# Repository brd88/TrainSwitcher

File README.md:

# TrainSwitcher
Microcomputer based management of train switches

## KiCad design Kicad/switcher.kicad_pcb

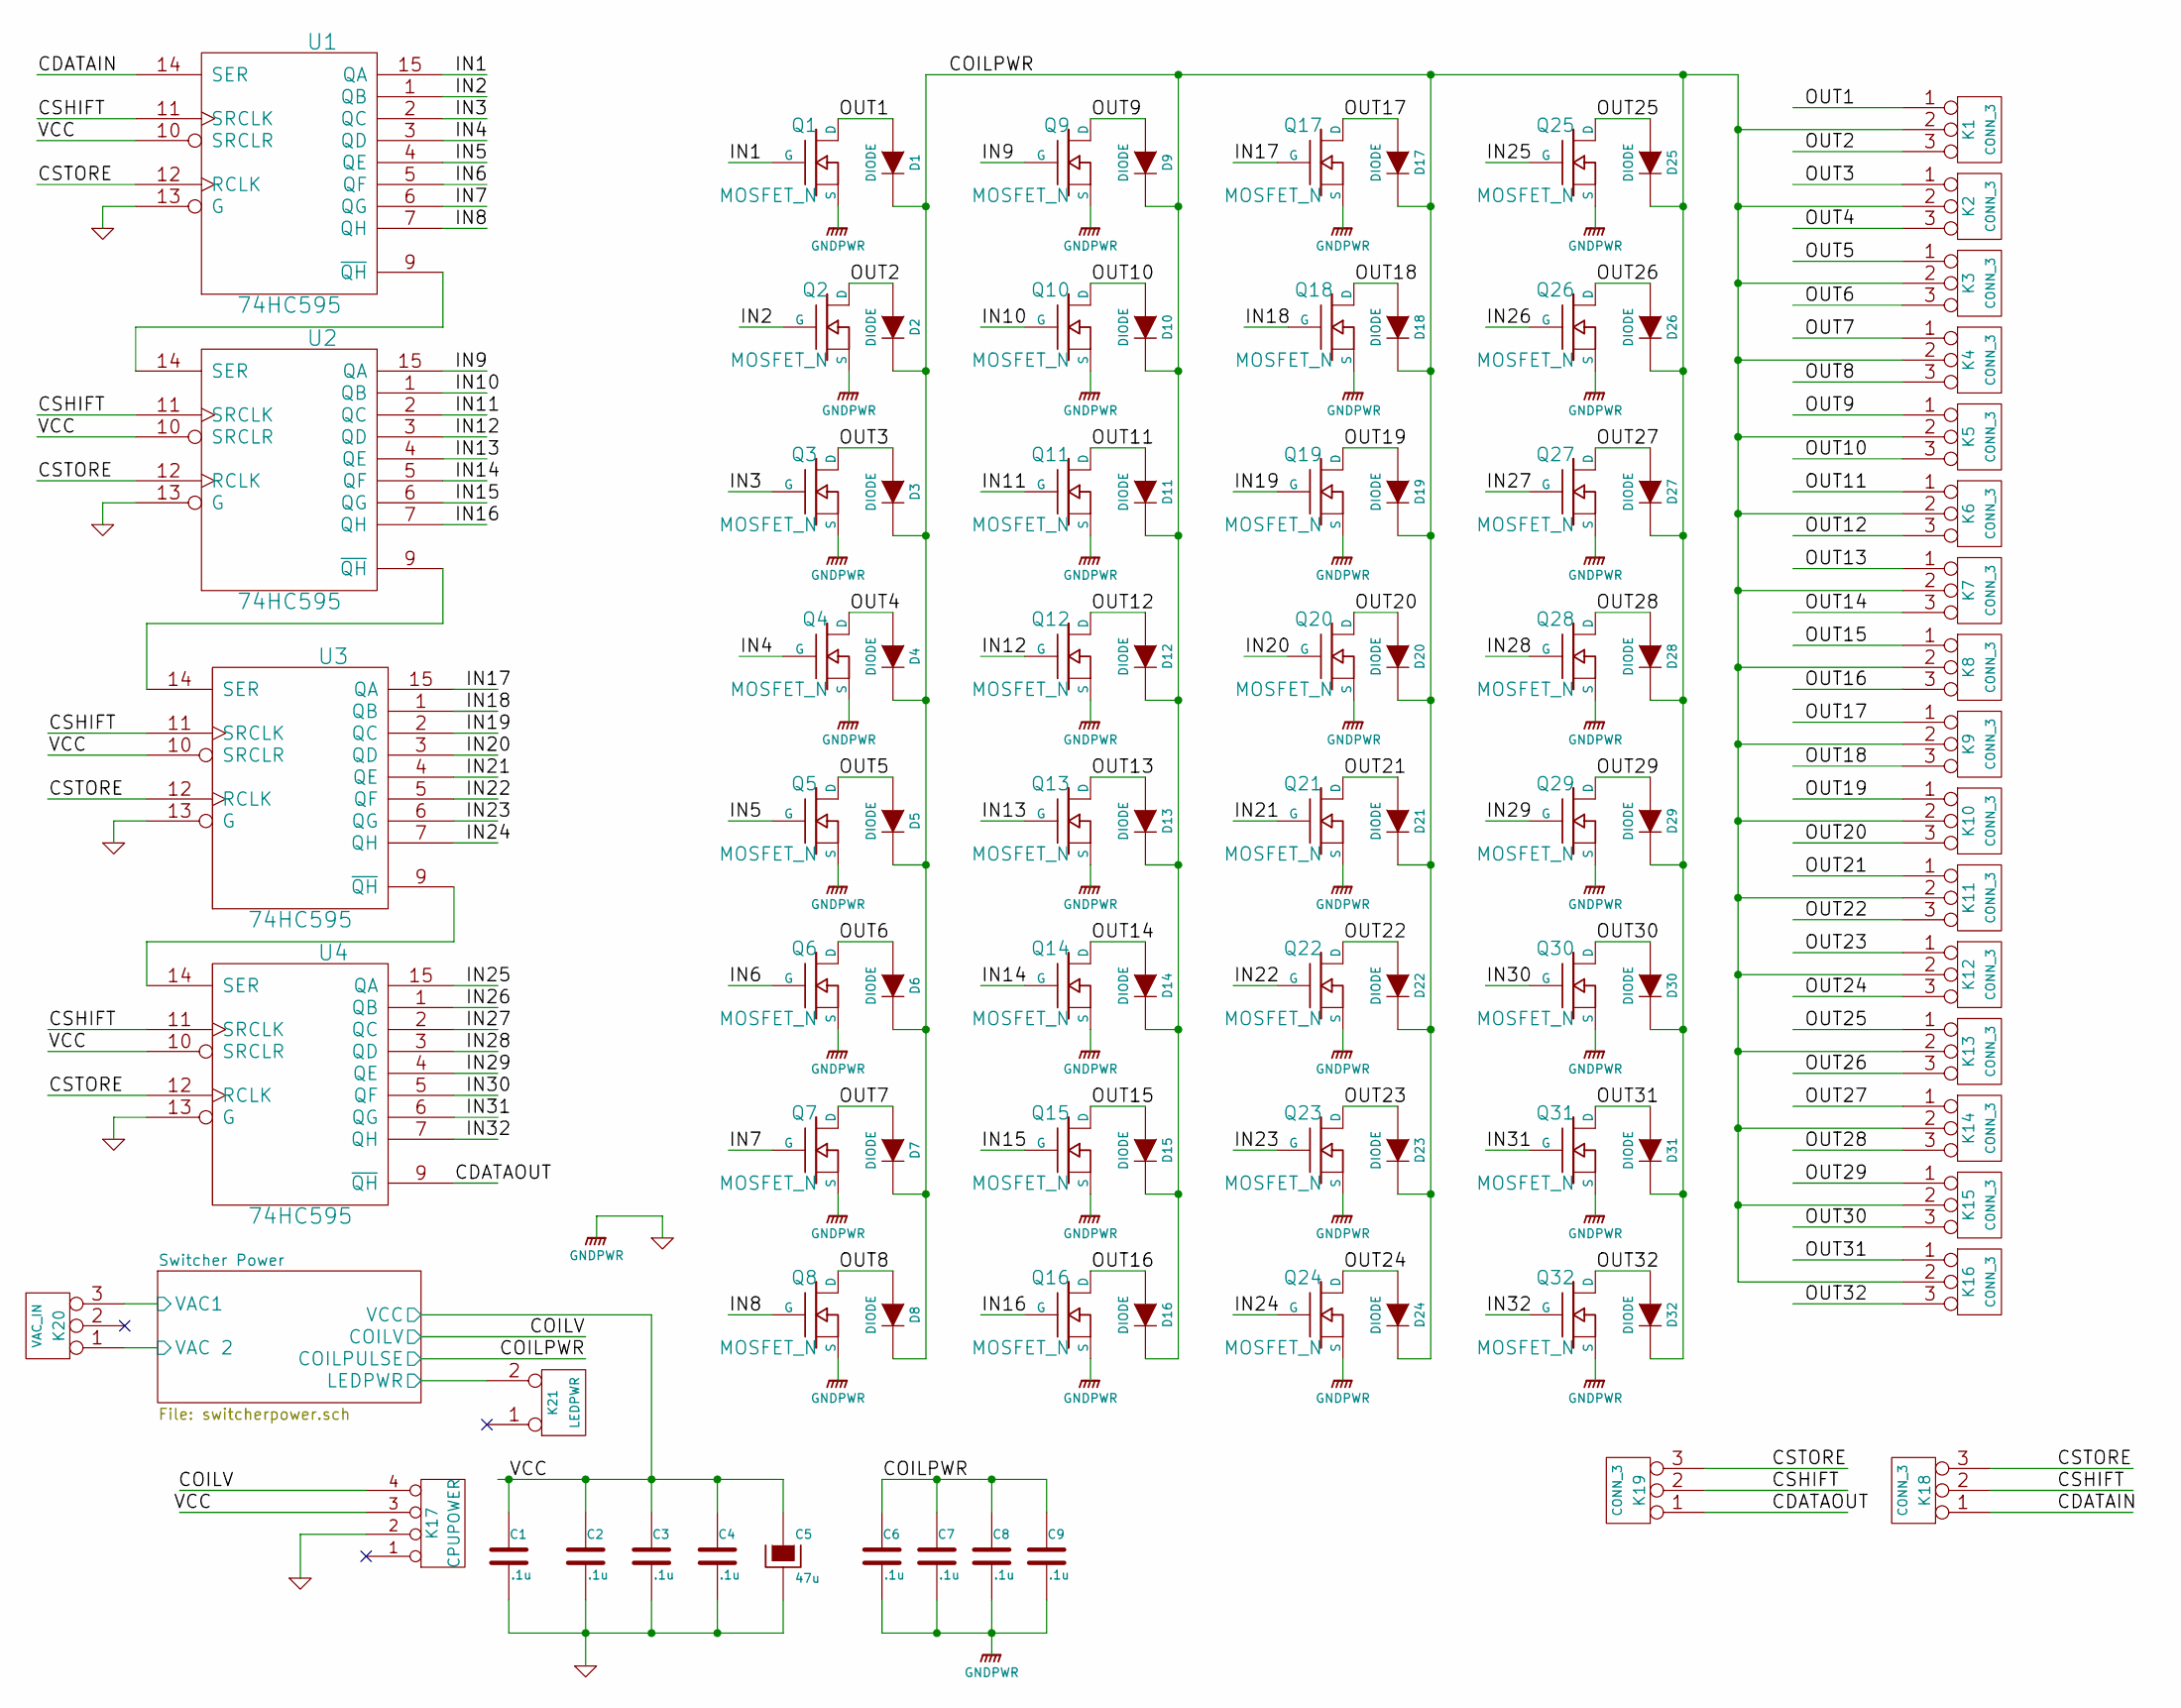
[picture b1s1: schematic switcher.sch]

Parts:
C1, C2, C3, C4, C6, C7, C8, C9: .1u
C5: 47u
D1, D2, D3, D4, D5, D6, D7, D8, D9, D10, D11, D12, D13, D14, D15, D16, D17, D18, D19, D20, D21, D22, D23, D24, D25, D26, D27, D28, D29, D30, D31, D32: DIODE
K1, K2, K3, K4, K5, K6, K7, K8, K9, K10, K11, K12, K13, K14, K15, K16, K18, K19: CONN_3
K17: CPUPOWER
K20: VAC_IN
K21: LEDPWR
Q1, Q2, Q3, Q4, Q5, Q6, Q7, Q8, Q9, Q10, Q11, Q12, Q13, Q14, Q15, Q16, Q17, Q18, Q19, Q20, Q21, Q22, Q23, Q24, Q25, Q26, Q27, Q28, Q29, Q30, Q31, Q32: MOSFET_N
U1, U2, U3, U4: 74HC595

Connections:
/CDATAIN: K18.1, U1.14 (SER)
/CDATAOUT: K19.1, U4.9 (~QH)
/CSHIFT: K18.2 (PM), K19.2 (PM), U1.11 (SRCLK), U2.11 (SRCLK), U3.11 (SRCLK), U4.11 (SRCLK)
/CSTORE: K18.3, K19.3, U1.12 (RCLK), U2.12 (RCLK), U3.12 (RCLK), U4.12 (RCLK)
/IN1: Q1.G, U1.15 (QA)
/IN2: Q2.G, U1.1 (QB)
/IN3: Q3.G, U1.2 (QC)
/IN4: Q4.G, U1.3 (QD)
/IN5: Q5.G, U1.4 (QE)
/IN6: Q6.G, U1.5 (QF)
/IN7: Q7.G, U1.6 (QG)
/IN8: Q8.G, U1.7 (QH)
/IN9: Q9.G, U2.15 (QA)
/IN10: Q10.G, U2.1 (QB)
/IN11: Q11.G, U2.2 (QC)
/IN12: Q12.G, U2.3 (QD)
/IN13: Q13.G, U2.4 (QE)
/IN14: Q14.G, U2.5 (QF)
/IN15: Q15.G, U2.6 (QG)
/IN16: Q16.G, U2.7 (QH)
/IN17: Q17.G, U3.15 (QA)
/IN18: Q18.G, U3.1 (QB)
/IN19: Q19.G, U3.2 (QC)
/IN20: Q20.G, U3.3 (QD)
/IN21: Q21.G, U3.4 (QE)
/IN22: Q22.G, U3.5 (QF)
/IN23: Q23.G, U3.6 (QG)
/IN24: Q24.G, U3.7 (QH)
/IN25: Q25.G, U4.15 (QA)
/IN26: Q26.G, U4.1 (QB)
/IN27: Q27.G, U4.2 (QC)
/IN28: Q28.G, U4.3 (QD)
/IN29: Q29.G, U4.4 (QE)
/IN30: Q30.G, U4.5 (QF)
/IN31: Q31.G, U4.6 (QG)
/IN32: Q32.G, U4.7 (QH)
/OUT1: D1.1 (A), K1.1, Q1.D
/OUT2: D2.1 (A), K1.3, Q2.D
/OUT3: D3.1 (A), K2.1, Q3.D
/OUT4: D4.1 (A), K2.3, Q4.D
/OUT5: D5.1 (A), K3.1, Q5.D
/OUT6: D6.1 (A), K3.3, Q6.D
/OUT7: D7.1 (A), K4.1, Q7.D
/OUT8: D8.1 (A), K4.3, Q8.D
/OUT9: D9.1 (A), K5.1, Q9.D
/OUT10: D10.1 (A), K5.3, Q10.D
/OUT11: D11.1 (A), K6.1, Q11.D
/OUT12: D12.1 (A), K6.3, Q12.D
/OUT13: D13.1 (A), K7.1, Q13.D
/OUT14: D14.1 (A), K7.3, Q14.D
/OUT15: D15.1 (A), K8.1, Q15.D
/OUT16: D16.1 (A), K8.3, Q16.D
/OUT17: D17.1 (A), K9.1, Q17.D
/OUT18: D18.1 (A), K9.3, Q18.D
/OUT19: D19.1 (A), K10.1, Q19.D
/OUT20: D20.1 (A), K10.3, Q20.D
/OUT21: D21.1 (A), K11.1, Q21.D
/OUT22: D22.1 (A), K11.3, Q22.D
/OUT23: D23.1 (A), K12.1, Q23.D
/OUT24: D24.1 (A), K12.3, Q24.D
/OUT25: D25.1 (A), K13.1, Q25.D
/OUT26: D26.1 (A), K13.3, Q26.D
/OUT27: D27.1 (A), K14.1, Q27.D
/OUT28: D28.1 (A), K14.3, Q28.D
/OUT29: D29.1 (A), K15.1, Q29.D
/OUT30: D30.1 (A), K15.3, Q30.D
/OUT31: D31.1 (A), K16.1, Q31.D
/OUT32: D32.1 (A), K16.3, Q32.D
/Switcher Power/COILPULSE: C6.1, C7.1, C8.1, C9.1, D1.2 (K), D2.2 (K), D3.2 (K), D4.2 (K), D5.2 (K), D6.2 (K), D7.2 (K), D8.2 (K), D9.2 (K), D10.2 (K), D11.2 (K), D12.2 (K), D13.2 (K), D14.2 (K), D15.2 (K), D16.2 (K), D17.2 (K), D18.2 (K), D19.2 (K), D20.2 (K), D21.2 (K), D22.2 (K), D23.2 (K), D24.2 (K), D25.2 (K), D26.2 (K), D27.2 (K), D28.2 (K), D29.2 (K), D30.2 (K), D31.2 (K), D32.2 (K), K1.2 (PM), K2.2 (PM), K3.2 (PM), K4.2 (PM), K5.2 (PM), K6.2 (PM), K7.2 (PM), K8.2 (PM), K9.2 (PM), K10.2 (PM), K11.2 (PM), K12.2 (PM), K13.2 (PM), K14.2 (PM), K15.2 (PM), K16.2 (PM); also elsewhere on the board
/Switcher Power/COILV: K17.4; also elsewhere on the board
/Switcher Power/LEDPWR: K21.2 (PM); also elsewhere on the board
/Switcher Power/VAC1: K20.3; also elsewhere on the board
/Switcher Power/VAC 2: K20.1; also elsewhere on the board
GND: C1.2, C2.2, C3.2, C4.2, C5.2, C6.2, C7.2, C8.2, C9.2, K17.2, Q1.S, Q2.S, Q3.S, Q4.S, Q5.S, Q6.S, Q7.S, Q8.S, Q9.S, Q10.S, Q11.S, Q12.S, Q13.S, Q14.S, Q15.S, Q16.S, Q17.S, Q18.S, Q19.S, Q20.S, Q21.S, Q22.S, Q23.S, Q24.S, Q25.S, Q26.S, Q27.S, Q28.S, Q29.S, Q30.S, Q31.S, Q32.S, U1.8 (GND), U1.13 (G), U2.8 (GND), U2.13 (G), U3.8 (GND), U3.13 (G), U4.8 (GND), U4.13 (G); also elsewhere on the board
unnamed: U1.9 (~QH), U2.14 (SER)
unnamed: U3.9 (~QH), U4.14 (SER)
unnamed: U2.9 (~QH), U3.14 (SER)
VCC: C1.1, C2.1, C3.1, C4.1, C5.1, K17.3, U1.10 (SRCLR), U1.16 (VCC), U2.10 (SRCLR), U2.16 (VCC), U3.10 (SRCLR), U3.16 (VCC), U4.10 (SRCLR), U4.16 (VCC); also elsewhere on the board

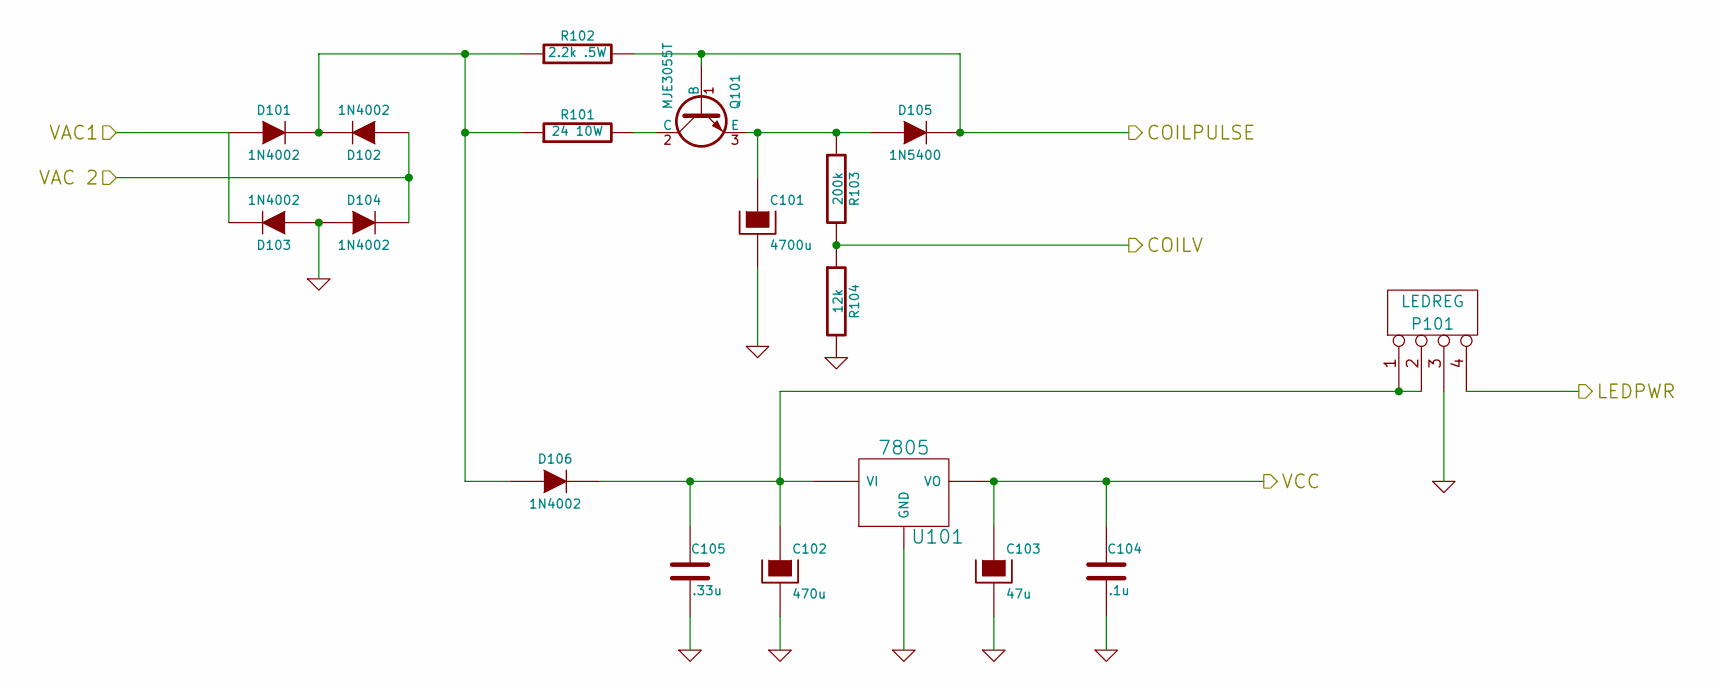
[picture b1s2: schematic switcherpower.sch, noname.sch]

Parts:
C101: 4700u
C102: 470u
C103: 47u
C104: .1u
C105: .33u
D101, D102, D103, D104, D106: 1N4002
D105: 1N5400
P101: LEDREG
Q101: MJE3055T; TO225
R101: 24 10W
R102: 2.2k .5W
R103: 200k
R104: 12k
U101: 7805

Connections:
/Switcher Power/COILPULSE: D105.2 (K), Q101.1 (B), R102.2; also elsewhere on the board
/Switcher Power/COILV: R103.2, R104.1; also elsewhere on the board
/Switcher Power/LEDPWR: P101.4; also elsewhere on the board
/Switcher Power/VAC1: D101.1 (A), D103.2 (K); also elsewhere on the board
/Switcher Power/VAC 2: D102.1 (A), D104.2 (K); also elsewhere on the board
GND: C101.2, C102.2, C103.2, C104.2, C105.2, D103.1 (A), D104.1 (A), P101.3, R104.2, U101.GND; also elsewhere on the board
unnamed: Q101.2 (C), R101.2
unnamed: C102.1, C105.1, D106.2 (K), P101.1, P101.2, U101.VI
unnamed: C101.1, D105.1 (A), Q101.3 (E), R103.1
unnamed: D101.2 (K), D102.2 (K), D106.1 (A), R101.1, R102.1
VCC: C103.1, C104.1, U101.VO; also elsewhere on the board

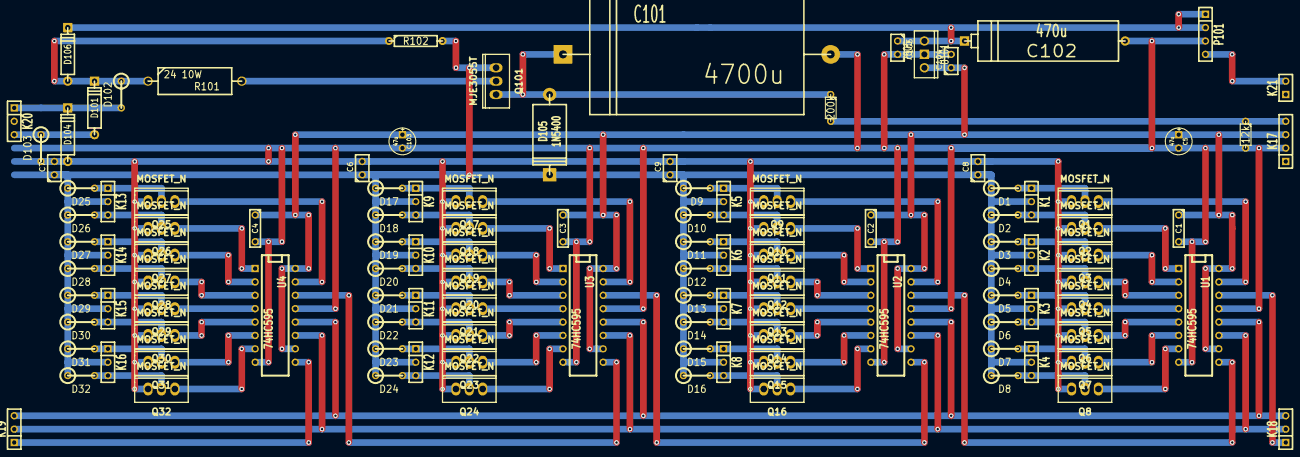
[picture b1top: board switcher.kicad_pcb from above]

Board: 2 copper layers, 117 parts (0 on the bottom side), 82 nets.

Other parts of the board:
Ref**: Val**; vero10x4

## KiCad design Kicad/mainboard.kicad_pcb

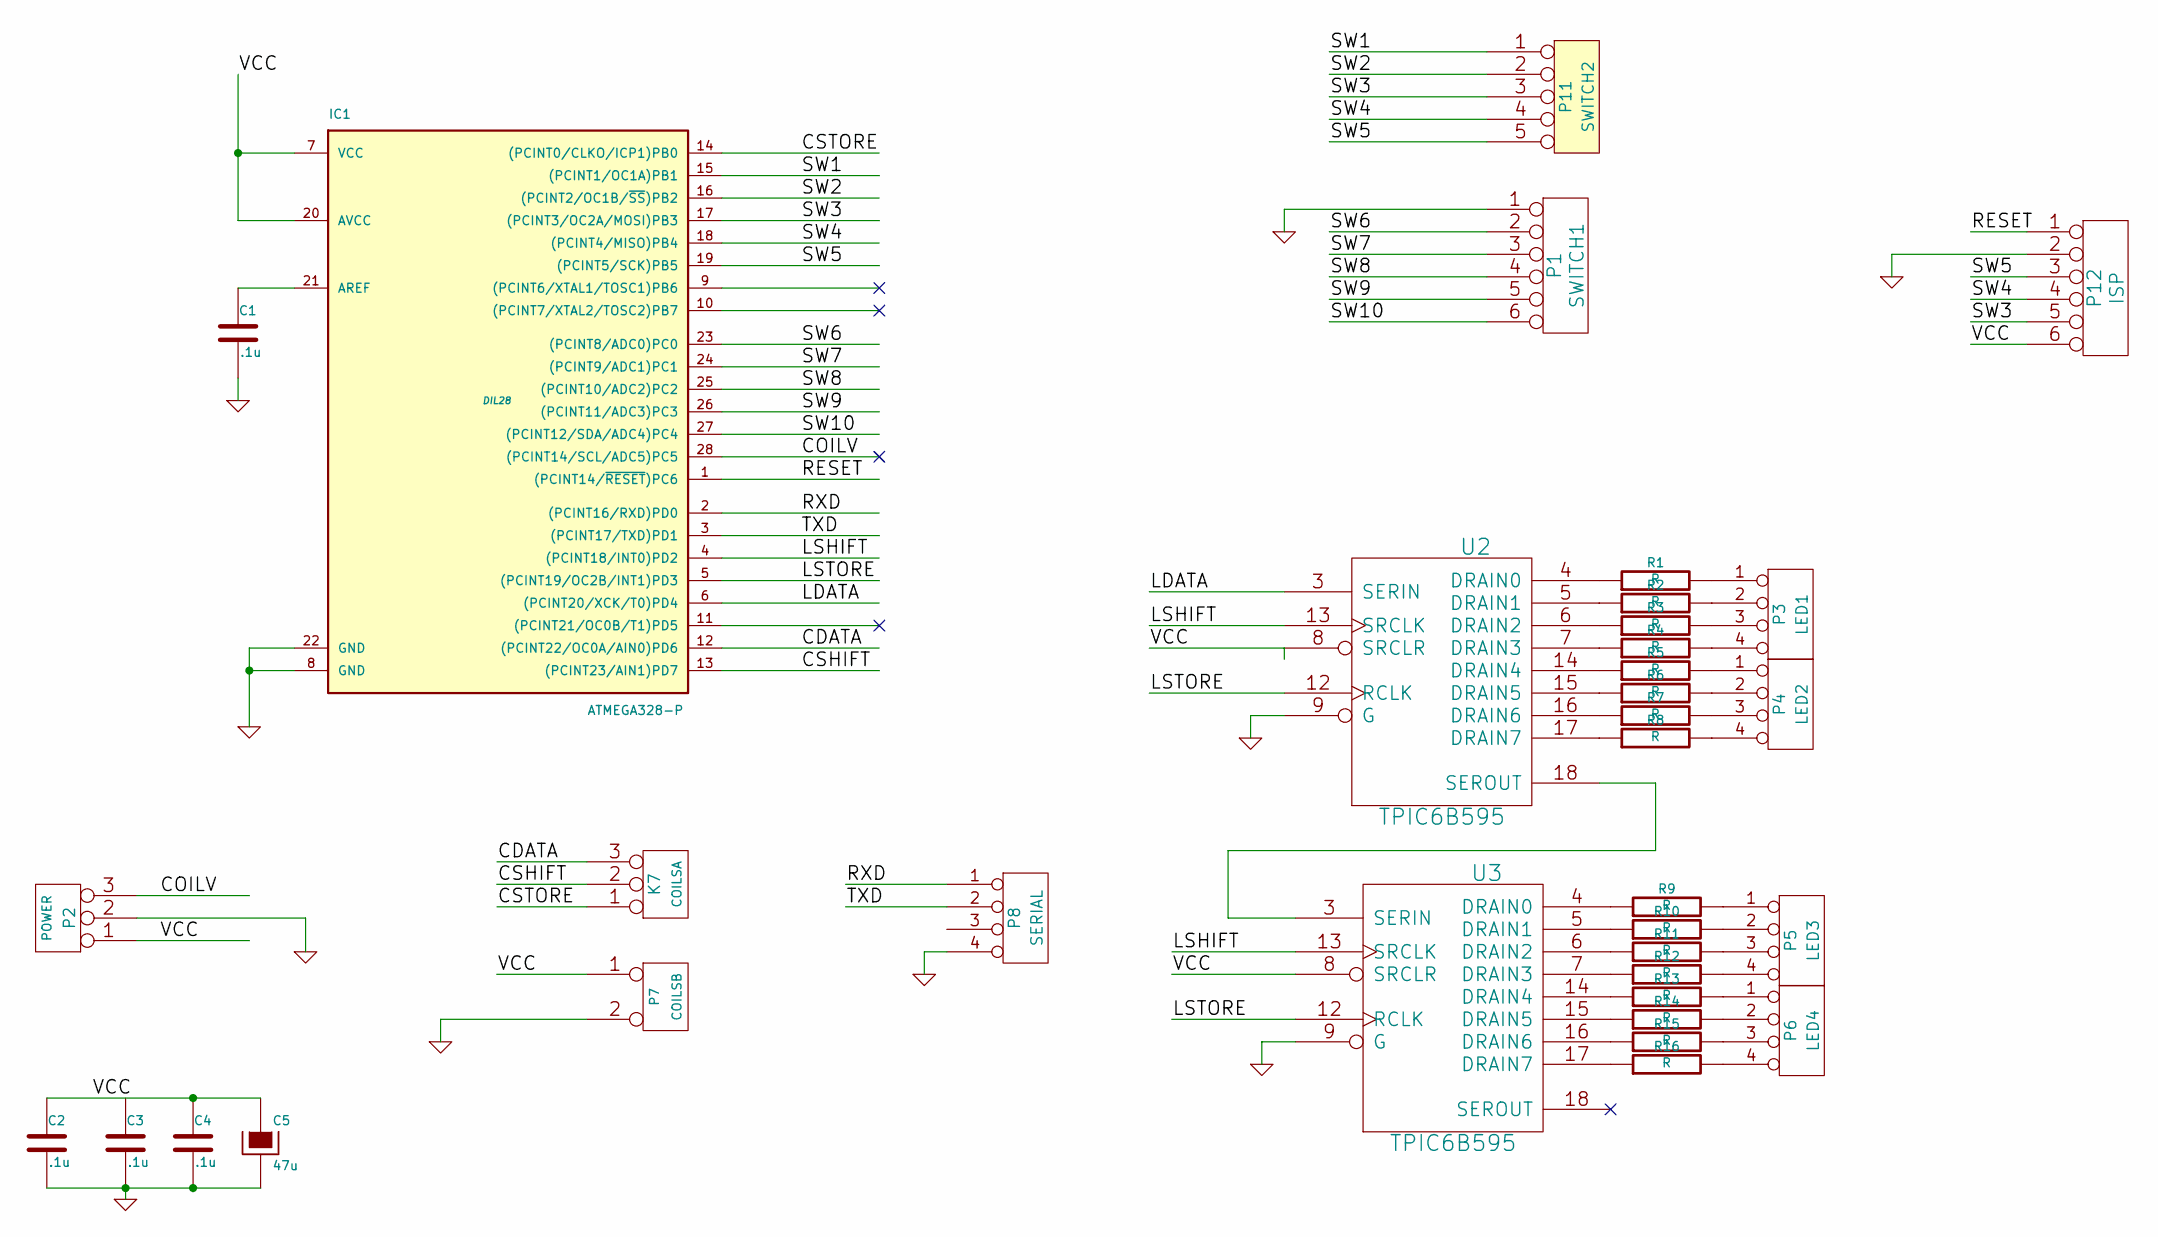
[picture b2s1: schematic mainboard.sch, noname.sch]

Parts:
C1, C2, C3, C4: .1u
C5: 47u
IC1: ATMEGA328-P; DIL28
K7: COILSA
P1: SWITCH1
P2: POWER
P3: LED1
P4: LED2
P5: LED3
P6: LED4
P7: COILSB
P8: SERIAL
P11: SWITCH2
P12: ISP
R1, R2, R3, R4, R5, R6, R7, R8, R9, R10, R11, R12, R13, R14, R15, R16: R
U2, U3: TPIC6B595

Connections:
/CDATA: IC1.12 ((PCINT22/OC0A/AIN0)PD6), K7.3
/COILV: IC1.28 ((PCINT14/SCL/ADC5)PC5), P2.3
/CSHIFT: IC1.13 ((PCINT23/AIN1)PD7), K7.2 (PM)
/CSTORE: IC1.14 ((PCINT0/CLKO/ICP1)PB0), K7.1
/LDATA: IC1.6 ((PCINT20/XCK/T0)PD4), U2.3 (SERIN)
/LSHIFT: IC1.4 ((PCINT18/INT0)PD2), U2.13 (SRCLK), U3.13 (SRCLK)
/LSTORE: IC1.5 ((PCINT19/OC2B/INT1)PD3), U2.12 (RCLK), U3.12 (RCLK)
/RESET: IC1.1 ((PCINT14/~RESET~)PC6), P12.1
/RXD: IC1.2 ((PCINT16/RXD)PD0), P8.1
/SW1: IC1.15 ((PCINT1/OC1A)PB1), P11.1
/SW2: IC1.16 ((PCINT2/OC1B/~SS~)PB2), P11.2
/SW3: IC1.17 ((PCINT3/OC2A/MOSI)PB3), P11.3, P12.5
/SW4: IC1.18 ((PCINT4/MISO)PB4), P11.4, P12.4
/SW5: IC1.19 ((PCINT5/SCK)PB5), P11.5, P12.3
/SW6: IC1.23 ((PCINT8/ADC0)PC0), P1.2
/SW7: IC1.24 ((PCINT9/ADC1)PC1), P1.3
/SW8: IC1.25 ((PCINT10/ADC2)PC2), P1.4
/SW9: IC1.26 ((PCINT11/ADC3)PC3), P1.5
/SW10: IC1.27 ((PCINT12/SDA/ADC4)PC4), P1.6
/TXD: IC1.3 ((PCINT17/TXD)PD1), P8.2
GND: C1.2, C2.2, C3.2, C4.2, C5.2, IC1.8 (GND), IC1.22 (GND), P1.1, P2.2 (PM), P7.2 (PM), P8.4, P12.2, U2.9 (G), U2.10 (GND), U2.11 (GND), U2.19 (GND), U3.9 (G), U3.10 (GND), U3.11 (GND), U3.19 (GND)
unnamed: C1.1, IC1.21 (AREF)
unnamed: R5.1, U2.14 (DRAIN4)
unnamed: P4.4, R8.2
unnamed: R8.1, U2.17 (DRAIN7)
unnamed: P4.3, R7.2
unnamed: R7.1, U2.16 (DRAIN6)
unnamed: P4.2, R6.2
unnamed: R6.1, U2.15 (DRAIN5)
unnamed: P4.1, R5.2
unnamed: P3.4, R4.2
unnamed: R4.1, U2.7 (DRAIN3)
unnamed: P3.3, R3.2
unnamed: R3.1, U2.6 (DRAIN2)
unnamed: P3.2, R2.2
unnamed: R2.1, U2.5 (DRAIN1)
unnamed: P3.1, R1.2
unnamed: R1.1, U2.4 (DRAIN0)
unnamed: P6.4, R16.2
unnamed: U2.18 (SEROUT), U3.3 (SERIN)
unnamed: R16.1, U3.17 (DRAIN7)
unnamed: R11.1, U3.6 (DRAIN2)
unnamed: P6.3, R15.2
unnamed: R15.1, U3.16 (DRAIN6)
unnamed: P6.2, R14.2
unnamed: R14.1, U3.15 (DRAIN5)
unnamed: P6.1, R13.2
unnamed: R13.1, U3.14 (DRAIN4)
unnamed: P5.4, R12.2
unnamed: R12.1, U3.7 (DRAIN3)
unnamed: P5.3, R11.2
unnamed: P5.2, R10.2
unnamed: R10.1, U3.5 (DRAIN1)
unnamed: P5.1, R9.2
unnamed: R9.1, U3.4 (DRAIN0)
VCC: C2.1, C4.1, C5.1, IC1.7 (VCC), IC1.20 (AVCC), P2.1, P7.1, P12.6, U2.2 (VCC), U2.8 (SRCLR), U3.2 (VCC), U3.8 (SRCLR)

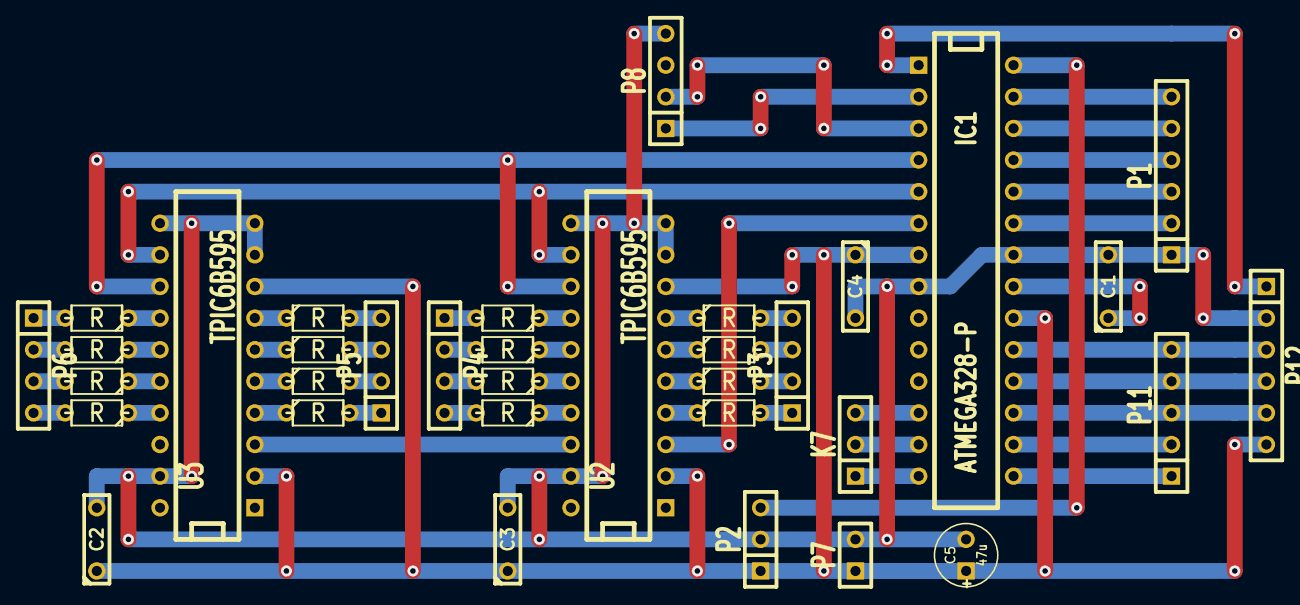
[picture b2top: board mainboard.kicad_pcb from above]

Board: 2 copper layers, 35 parts (0 on the bottom side), 56 nets.

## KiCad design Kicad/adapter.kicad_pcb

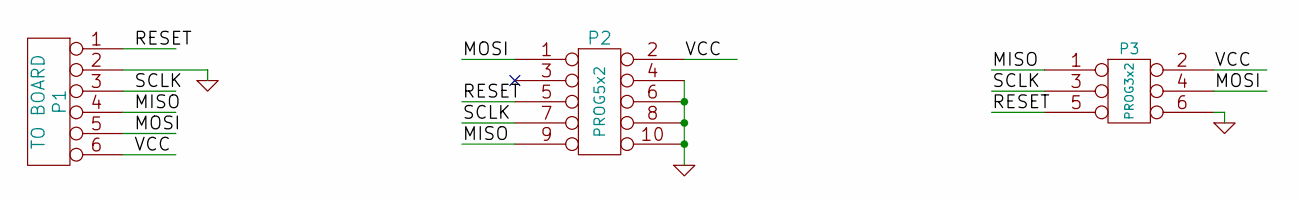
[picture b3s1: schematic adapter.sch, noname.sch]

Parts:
P1: TO BOARD
P2: PROG5x2
P3: PROG3x2

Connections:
/MISO: P1.4, P2.9, P3.1
/MOSI: P1.5, P2.1, P3.4
/RESET: P1.1, P2.5, P3.5
/SCLK: P1.3, P2.7, P3.3
/VCC: P1.6, P2.2, P3.2
GND: P1.2, P2.4, P2.6, P2.8, P2.10, P3.6

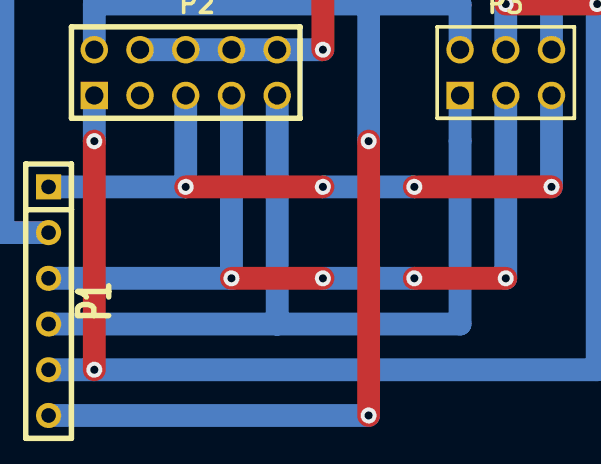
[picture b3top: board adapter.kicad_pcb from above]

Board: 2 copper layers, 4 parts (0 on the bottom side), 6 nets.

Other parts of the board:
Ref**: Val**; board

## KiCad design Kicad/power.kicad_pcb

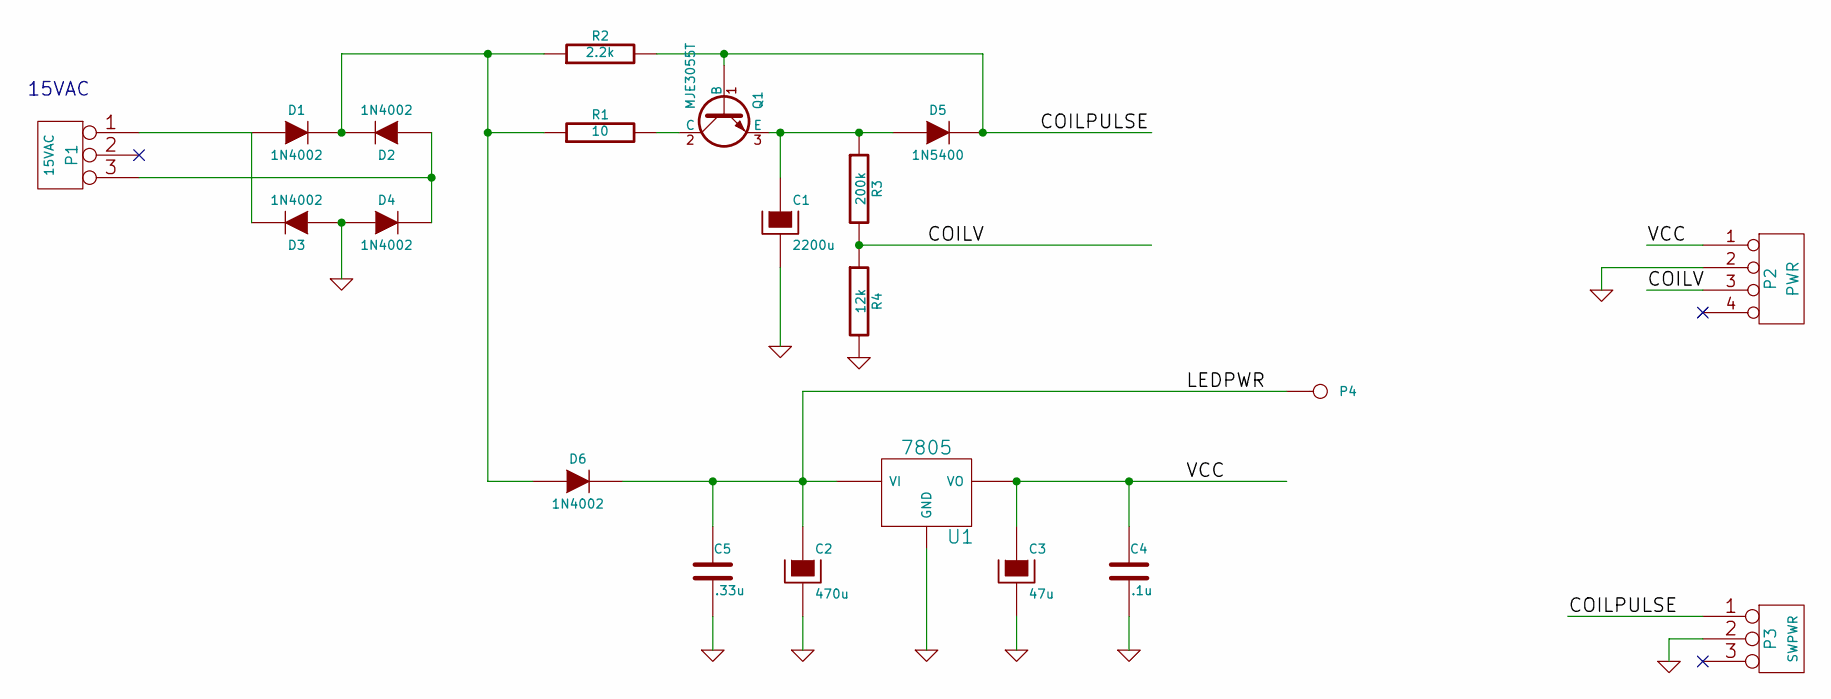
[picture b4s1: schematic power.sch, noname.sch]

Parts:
C1: 2200u
C2: 470u
C3: 47u
C4: .1u
C5: .33u
D1, D2, D3, D4, D6: 1N4002
D5: 1N5400
P1: 15VAC
P2: PWR
P3: SWPWR
P4: LEDPWR
Q1: MJE3055T; TO225
R1: 10
R2: 2.2k
R3: 200k
R4: 12k
U1: 7805

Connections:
/COILPULSE: D5.2 (K), P3.1, Q1.1 (B), R2.2
/COILV: P2.3, R3.2, R4.1
/LEDPWR: C2.1, C5.1, D6.2 (K), P4.1, U1.VI
/VCC: C3.1, C4.1, P2.1, U1.VO
GND: C1.2, C2.2, C3.2, C4.2, C5.2, D3.1 (A), D4.1 (A), P2.2, P3.2 (PM), R4.2, U1.GND
unnamed: Q1.2 (C), R1.2
unnamed: D1.2 (K), D2.2 (K), D6.1 (A), R1.1, R2.1
unnamed: D2.1 (A), D4.2 (K), P1.3
unnamed: D1.1 (A), D3.2 (K), P1.1
unnamed: C1.1, D5.1 (A), Q1.3 (E), R3.1

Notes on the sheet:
15VAC

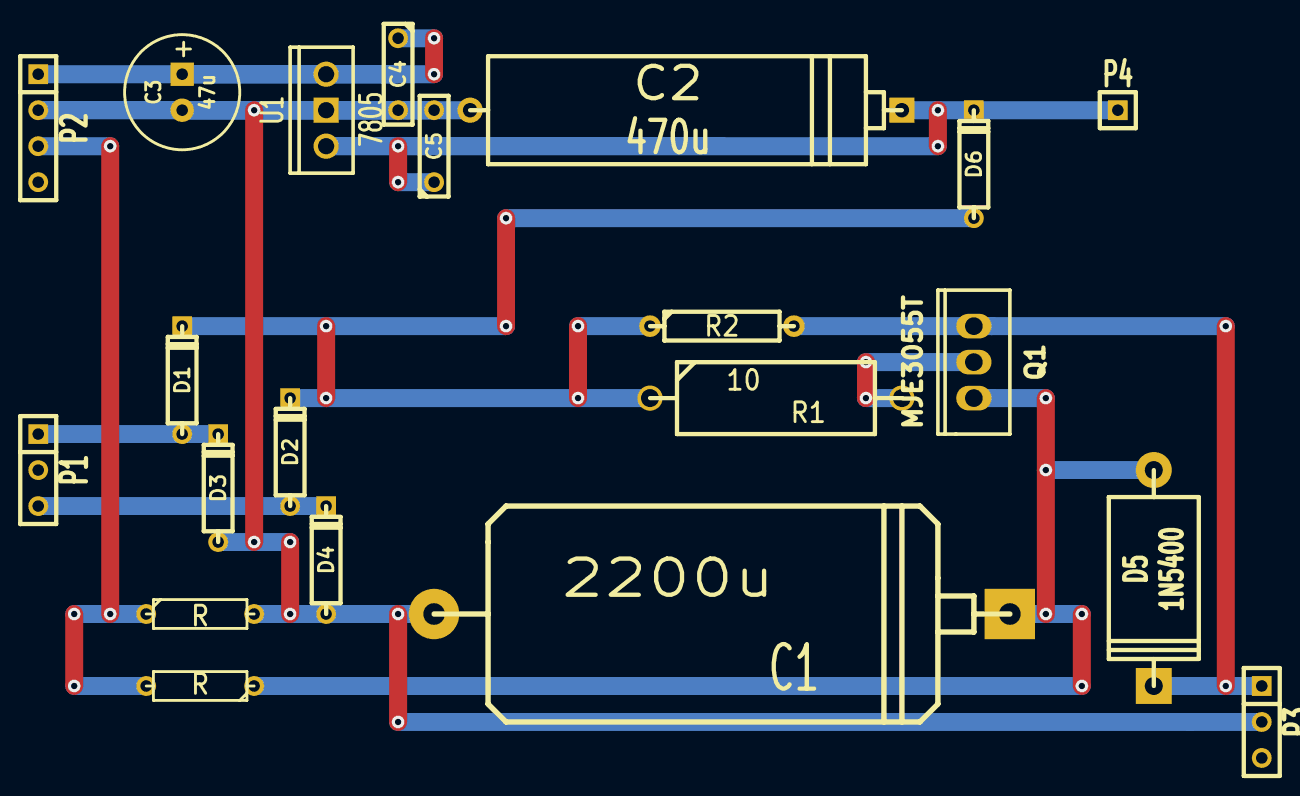
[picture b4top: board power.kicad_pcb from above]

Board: 2 copper layers, 22 parts (0 on the bottom side), 10 nets.

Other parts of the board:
Ref**: Val**; board2

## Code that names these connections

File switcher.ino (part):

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
// 0 and 1 are used for the serial port

const uint8_t lshift = 2;
const uint8_t lstore = 3;
const uint8_t ldata = 4;

// 5 is unused

const uint8_t cdata  = 6;
const uint8_t cshift = 7;
const uint8_t cstore = 8;

const uint8_t sw1 = A4;
const uint8_t sw2 = A3;
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const uint8_t sw9 = 10;
const uint8_t sw10 = 9;

const uint8_t coilv = A5;

unsigned long lastMillis = 0;
unsigned int vhi;
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    // Initialize ports for coil shift register
    // OUTPUT with initial value == 0

    pinMode(cdata, OUTPUT);
    pinMode(cshift, OUTPUT);
    pinMode(cstore, OUTPUT);
    digitalWrite(cdata, LOW);
    digitalWrite(cshift, LOW);
    digitalWrite(cstore, LOW);
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
    // Initialize ports for LED shift registers
    // OUTPUT with initial value = 0
    pinMode(ldata, OUTPUT);
    pinMode(lshift, OUTPUT);
    pinMode(lstore, OUTPUT);
    digitalWrite(ldata, LOW);
    digitalWrite(lshift, LOW);
    digitalWrite(lstore, LOW);
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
